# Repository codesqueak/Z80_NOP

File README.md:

# Z80 NOP Tester v1.2 

Z80 CPU NOP Instruction Tester

## Introduction

This board has been designed to allow a Z80 to run NOP instructions slowly enough to see address and various control lines to aid in diagnostics

In Z80 assembly, NOP (No Operation) is the opcode 0x00.

When executed, the CPU does nothing for one machine cycle and then increments the program counter (PC) to fetch the next instruction.

## What it Tests
* Clock circuit (CPU is being driven)
* Reset circuit (PC starts at 0x0000)
* Address bus (sequential counting)
* Basic instruction fetch and decode mechanism

## What You Can See
* A display of the address bus contents as it increments
* Status of RFSH, M1, MREQ and RD signals

## What You Can Measure
* Test points for clock, 0V and 5V
* Test points for s RFSH, M1, MREQ, RD IORQ, WR, HALT, BUSACK (Useful if your Z80 is mis-behaving)

# Z80 NOP HALT Tester v2.1

Z80 CPU NOP HALT Instruction Tester

## Introduction

An extended version of the board which allows the use of HALT instructions to test dynamic memory refresh operations

In Z80 assembly, HALT is the opcode 0x76.

When executed, the CPU enters HALT mode and ceases executing except for memory refresh operations

## Documentation

For full documentation, see the [NOP pdf here](Z80_NOP.pdf) and [NOP HALT pdf here](Z80_NOP_HALT.pdf)

## Release 1.2 Boards

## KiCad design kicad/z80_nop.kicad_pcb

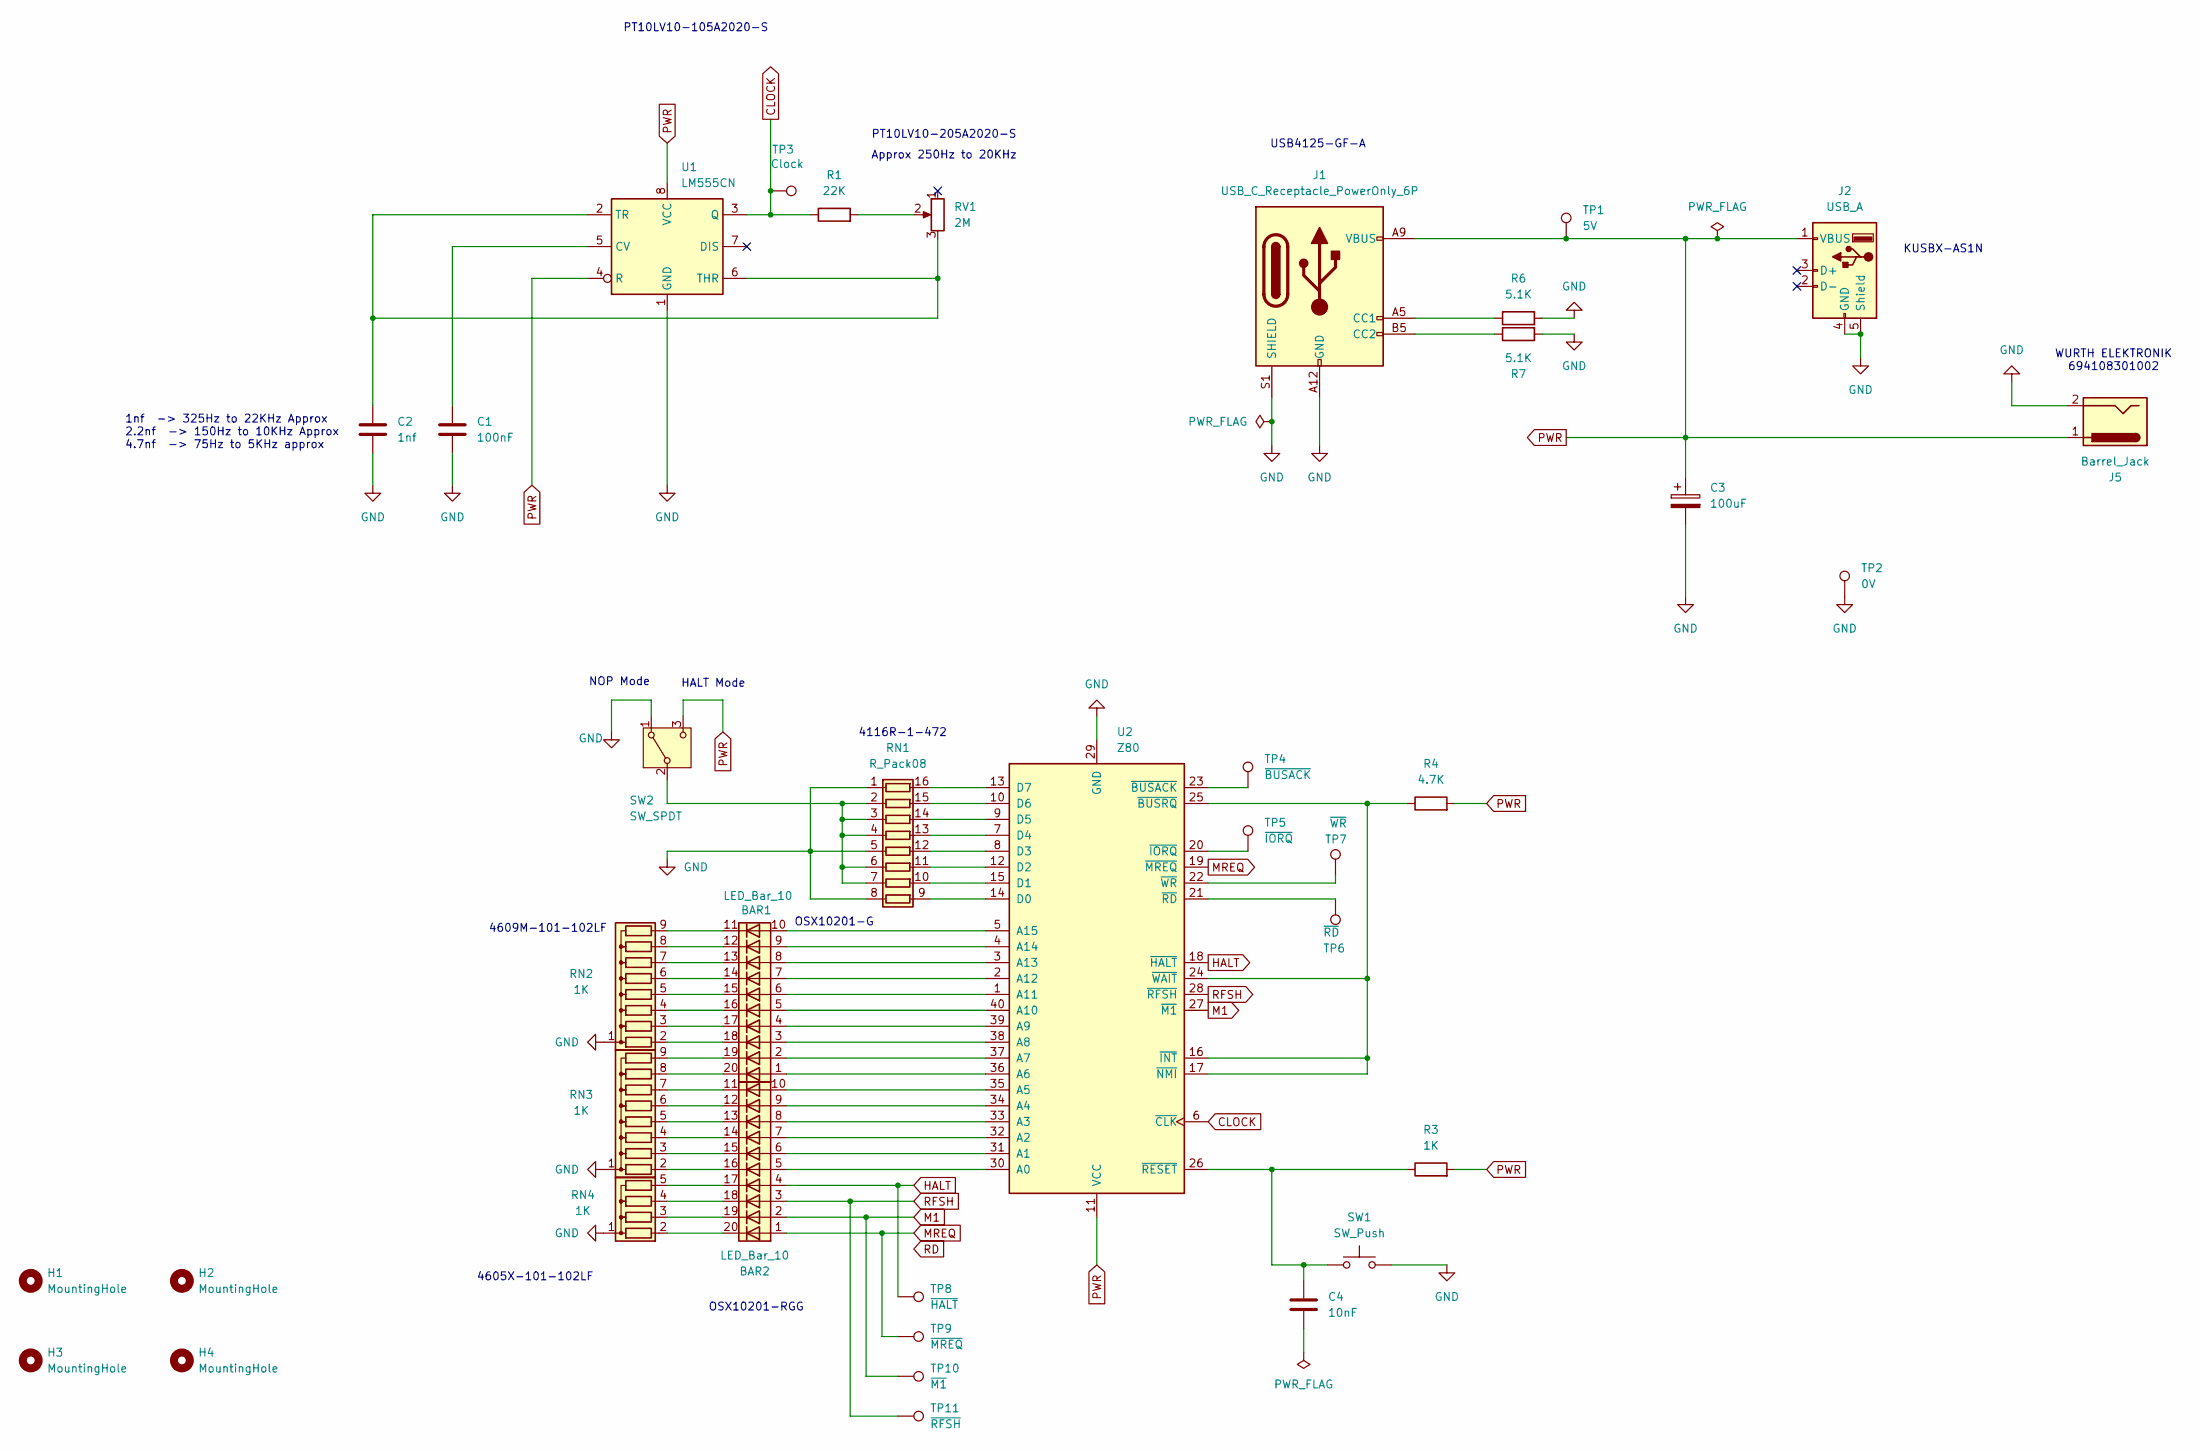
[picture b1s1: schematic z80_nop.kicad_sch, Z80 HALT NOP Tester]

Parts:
BAR1, BAR2: LED_Bar_10; DIP-20_W7.62mm
C1: 100nF; C_Disc_D6.0mm_W2.5mm_P5.00mm
C2: 1nf; C_Disc_D6.0mm_W2.5mm_P5.00mm
C3: 100uF; CP_Radial_D5.0mm_P2.50mm
C4: 10nF; C_Disc_D6.0mm_W2.5mm_P5.00mm
H1, H2, H3, H4: MountingHole; MountingHole_3.5mm
J1: USB_C_Receptacle_PowerOnly_6P; USB_C_Receptacle_GCT_USB4125-xx-x-0190_6P_TopMnt_Horizontal
J2: USB_A; USB_A_Kycon_KUSBX-AS1N-B_Horizontal
J5: Barrel_Jack; BarrelJack_Wuerth_6941xx301002
R1: 22K; R_Axial_DIN0309_L9.0mm_D3.2mm_P12.70mm_Horizontal
R3: 1K; R_Axial_DIN0309_L9.0mm_D3.2mm_P12.70mm_Horizontal
R4: 4.7K; R_Axial_DIN0309_L9.0mm_D3.2mm_P12.70mm_Horizontal
R6, R7: 5.1K; R_Axial_DIN0309_L9.0mm_D3.2mm_P12.70mm_Horizontal
RN1: R_Pack08; DIP-16_W7.62mm
RN2, RN3: 1K; R_Array_SIP9
RN4: 1K; R_Array_SIP5
RV1: 2M; Potentiometer_Piher_PT-10-V10_Vertical
SW1: SW_Push; SW_PUSH_6mm_H5mm
SW2: SW_SPDT; SW_Slide-03_Pin-2-Common_10x2.5x6.4_P2.54mm
TP1: 5V; TestPoint_THTPad_2.0x2.0mm_Drill1.0mm
TP2: 0V; TestPoint_THTPad_2.0x2.0mm_Drill1.0mm
TP3: Clock; TestPoint_THTPad_2.0x2.0mm_Drill1.0mm
TP4: ~{BUSACK}; TestPoint_THTPad_2.0x2.0mm_Drill1.0mm
TP5: ~{IORQ}; TestPoint_THTPad_2.0x2.0mm_Drill1.0mm
TP6: ~{RD}; TestPoint_THTPad_2.0x2.0mm_Drill1.0mm
TP7: ~{WR}; TestPoint_THTPad_2.0x2.0mm_Drill1.0mm
TP8: ~{HALT}; TestPoint_THTPad_2.0x2.0mm_Drill1.0mm
TP9: ~{MREQ}; TestPoint_THTPad_2.0x2.0mm_Drill1.0mm
TP10: ~{M1}; TestPoint_THTPad_2.0x2.0mm_Drill1.0mm
TP11: ~{RFSH}; TestPoint_THTPad_2.0x2.0mm_Drill1.0mm
U1: LM555CN; DIP-8_W7.62mm
U2: Z80; DIP_Socket-40_W11.9_W12.7_W15.24_W17.78_W18.5_ZIF

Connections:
CLOCK: R1.1, TP3.1, U1.3 (Q), U2.6 (~CLK)
GND: C1.2, C2.2, C3.2, J1.A12 (GND), J1.B12 (GND), J1.S1 (SHIELD), J2.4 (GND), J2.5 (Shield), J5.2, R6.2, R7.2, RN1.1 (R1.1), RN1.5 (R5.1), RN1.8 (R8.1), RN2.1 (common), RN3.1 (common), RN4.1 (common), SW1.2, SW2.1 (A), TP2.1, U1.1 (GND), U2.29 (GND)
HALT: BAR2.4 (A), TP8.1, U2.18 (~HALT)
M1: BAR2.2 (A), TP10.1, U2.27 (~M1)
MREQ: BAR2.1 (A), TP9.1, U2.19 (~MREQ)
unnamed: J1.A5 (CC1), R6.1
unnamed: J1.B5 (CC2), R7.1
unnamed: R1.2, RV1.2
unnamed: RN1.16 (R1.2), U2.13 (D7)
unnamed: RN1.2 (R2.1), RN1.3 (R3.1), RN1.4 (R4.1), RN1.6 (R6.1), RN1.7 (R7.1), SW2.2 (B)
unnamed: RN1.15 (R2.2), U2.10 (D6)
unnamed: RN1.14 (R3.2), U2.9 (D5)
unnamed: RN1.13 (R4.2), U2.7 (D4)
unnamed: RN1.12 (R5.2), U2.8 (D3)
unnamed: RN1.11 (R6.2), U2.12 (D2)
unnamed: RN1.10 (R7.2), U2.15 (D1)
unnamed: RN1.9 (R8.2), U2.14 (D0)
unnamed: BAR1.18 (K), RN2.2 (R1)
unnamed: BAR1.17 (K), RN2.3 (R2)
unnamed: BAR1.16 (K), RN2.4 (R3)
unnamed: BAR1.15 (K), RN2.5 (R4)
unnamed: BAR1.14 (K), RN2.6 (R5)
unnamed: BAR1.13 (K), RN2.7 (R6)
unnamed: BAR1.12 (K), RN2.8 (R7)
unnamed: BAR1.11 (K), RN2.9 (R8)
unnamed: BAR2.16 (K), RN3.2 (R1)
unnamed: BAR2.15 (K), RN3.3 (R2)
unnamed: BAR2.14 (K), RN3.4 (R3)
unnamed: BAR2.13 (K), RN3.5 (R4)
unnamed: BAR2.12 (K), RN3.6 (R5)
unnamed: BAR2.11 (K), RN3.7 (R6)
unnamed: BAR1.20 (K), RN3.8 (R7)
unnamed: BAR1.19 (K), RN3.9 (R8)
unnamed: BAR2.20 (K), RN4.2 (R1)
unnamed: BAR2.19 (K), RN4.3 (R2)
unnamed: BAR2.18 (K), RN4.4 (R3)
unnamed: BAR2.17 (K), RN4.5 (R4)
unnamed: C1.1, U1.5 (CV)
unnamed: C2.1, RV1.3, U1.2 (TR), U1.6 (THR)
unnamed: BAR2.5 (A), U2.30 (A0)
unnamed: BAR2.6 (A), U2.31 (A1)
unnamed: BAR2.7 (A), U2.32 (A2)
unnamed: BAR2.8 (A), U2.33 (A3)
unnamed: BAR2.9 (A), U2.34 (A4)
unnamed: BAR2.10 (A), U2.35 (A5)
unnamed: BAR1.1 (A), U2.36 (A6)
unnamed: BAR1.2 (A), U2.37 (A7)
unnamed: BAR1.3 (A), U2.38 (A8)
unnamed: BAR1.4 (A), U2.39 (A9)
unnamed: BAR1.5 (A), U2.40 (A10)
unnamed: BAR1.6 (A), U2.1 (A11)
unnamed: BAR1.7 (A), U2.2 (A12)
unnamed: BAR1.8 (A), U2.3 (A13)
unnamed: BAR1.9 (A), U2.4 (A14)
unnamed: BAR1.10 (A), U2.5 (A15)
unnamed: TP4.1, U2.23 (~BUSACK)
unnamed: R4.1, U2.16 (~INT), U2.17 (~NMI), U2.24 (~WAIT), U2.25 (~BUSRQ)
unnamed: TP5.1, U2.20 (~IORQ)
unnamed: TP6.1, U2.21 (~RD)
unnamed: C4.1, R3.1, SW1.1, U2.26 (~RESET)
unnamed: TP7.1, U2.22 (~WR)
PWR: C3.1, J1.A9 (VBUS), J1.B9 (VBUS), J2.1 (VBUS), J5.1, R3.2, R4.2, SW2.3 (C), TP1.1, U1.4 (R), U1.8 (VCC), U2.11 (VCC)
RFSH: BAR2.3 (A), TP11.1, U2.28 (~RFSH)

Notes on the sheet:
4116R-1-472
USB4125-GF-A
4605X-101-102LF
OSX10201-G
OSX10201-RGG
Approx 250Hz to 20KHz
KUSBX-AS1N
NOP Mode
4609M-101-102LF
HALT Mode
PT10LV10-205A2020-S
WURTH ELEKTRONIK 694108301002
PT10LV10-105A2020-S
1nf -> 325Hz to 22KHz Approx 2.2nf -> 150Hz to 10KHz Approx 4.7nf -> 75Hz to 5KHz approx

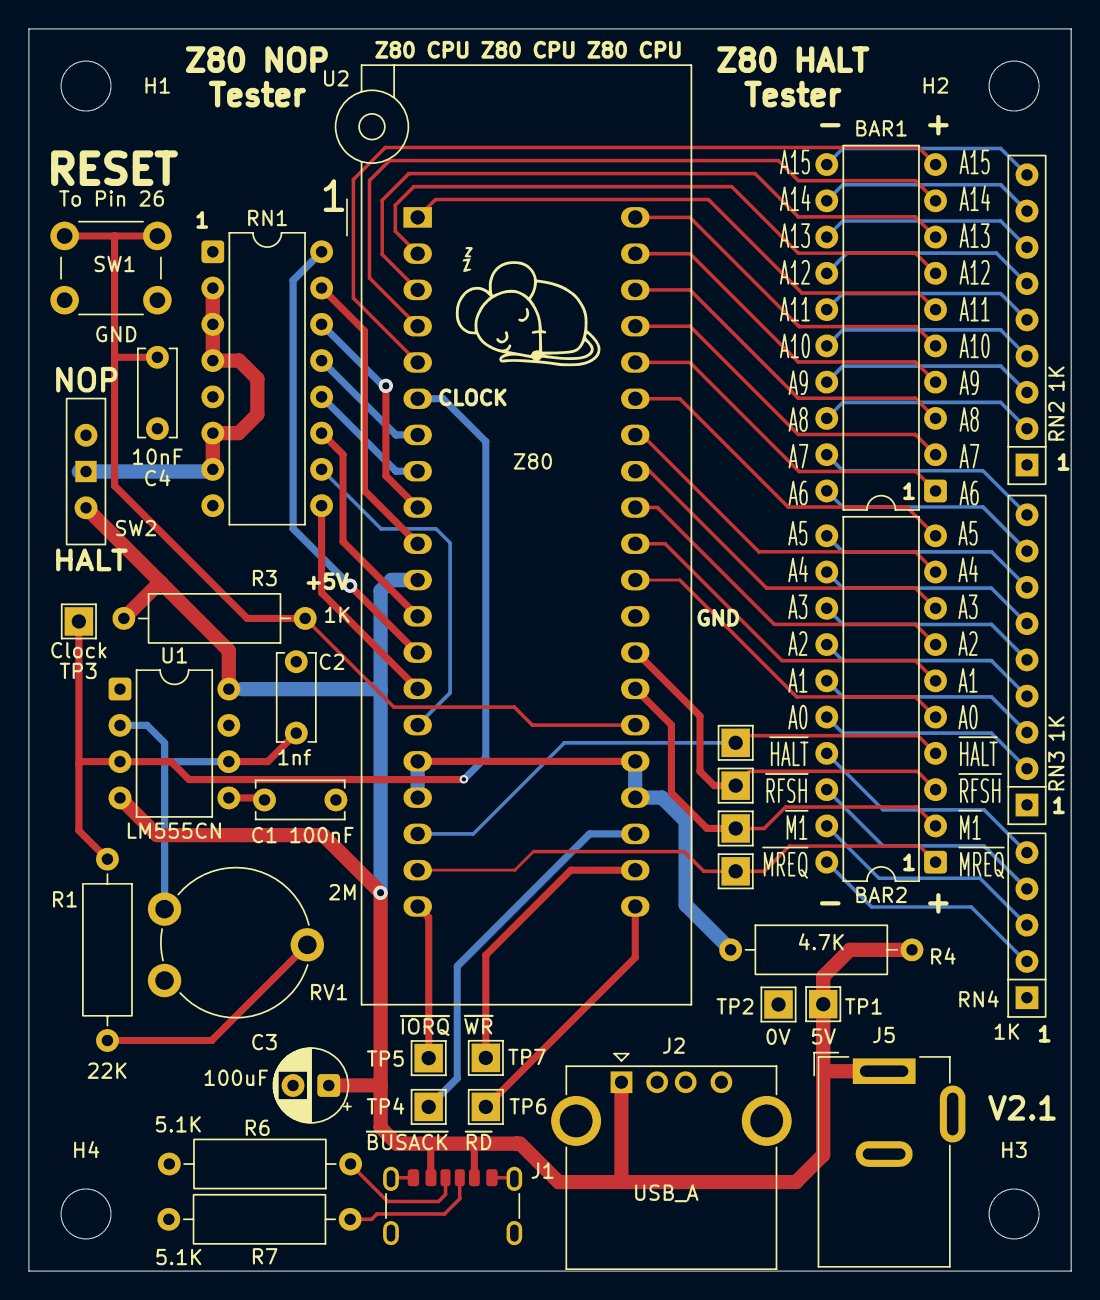
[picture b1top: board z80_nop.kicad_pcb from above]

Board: 2 copper layers, 73.0 x 87.0 mm, 40 parts (1 on the bottom side), 63 nets.

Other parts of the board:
G001, G002: LOGO; sleepymouse_very_very_small

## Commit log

2025-06-28 Initial upload
2025-06-28 Update PCB
2025-08-10 Minor tweaks
2025-08-13 Docs
2026-01-08 Update docs
2026-02-06 Add HALT mode
2026-02-06 Update docs, add gerbers
